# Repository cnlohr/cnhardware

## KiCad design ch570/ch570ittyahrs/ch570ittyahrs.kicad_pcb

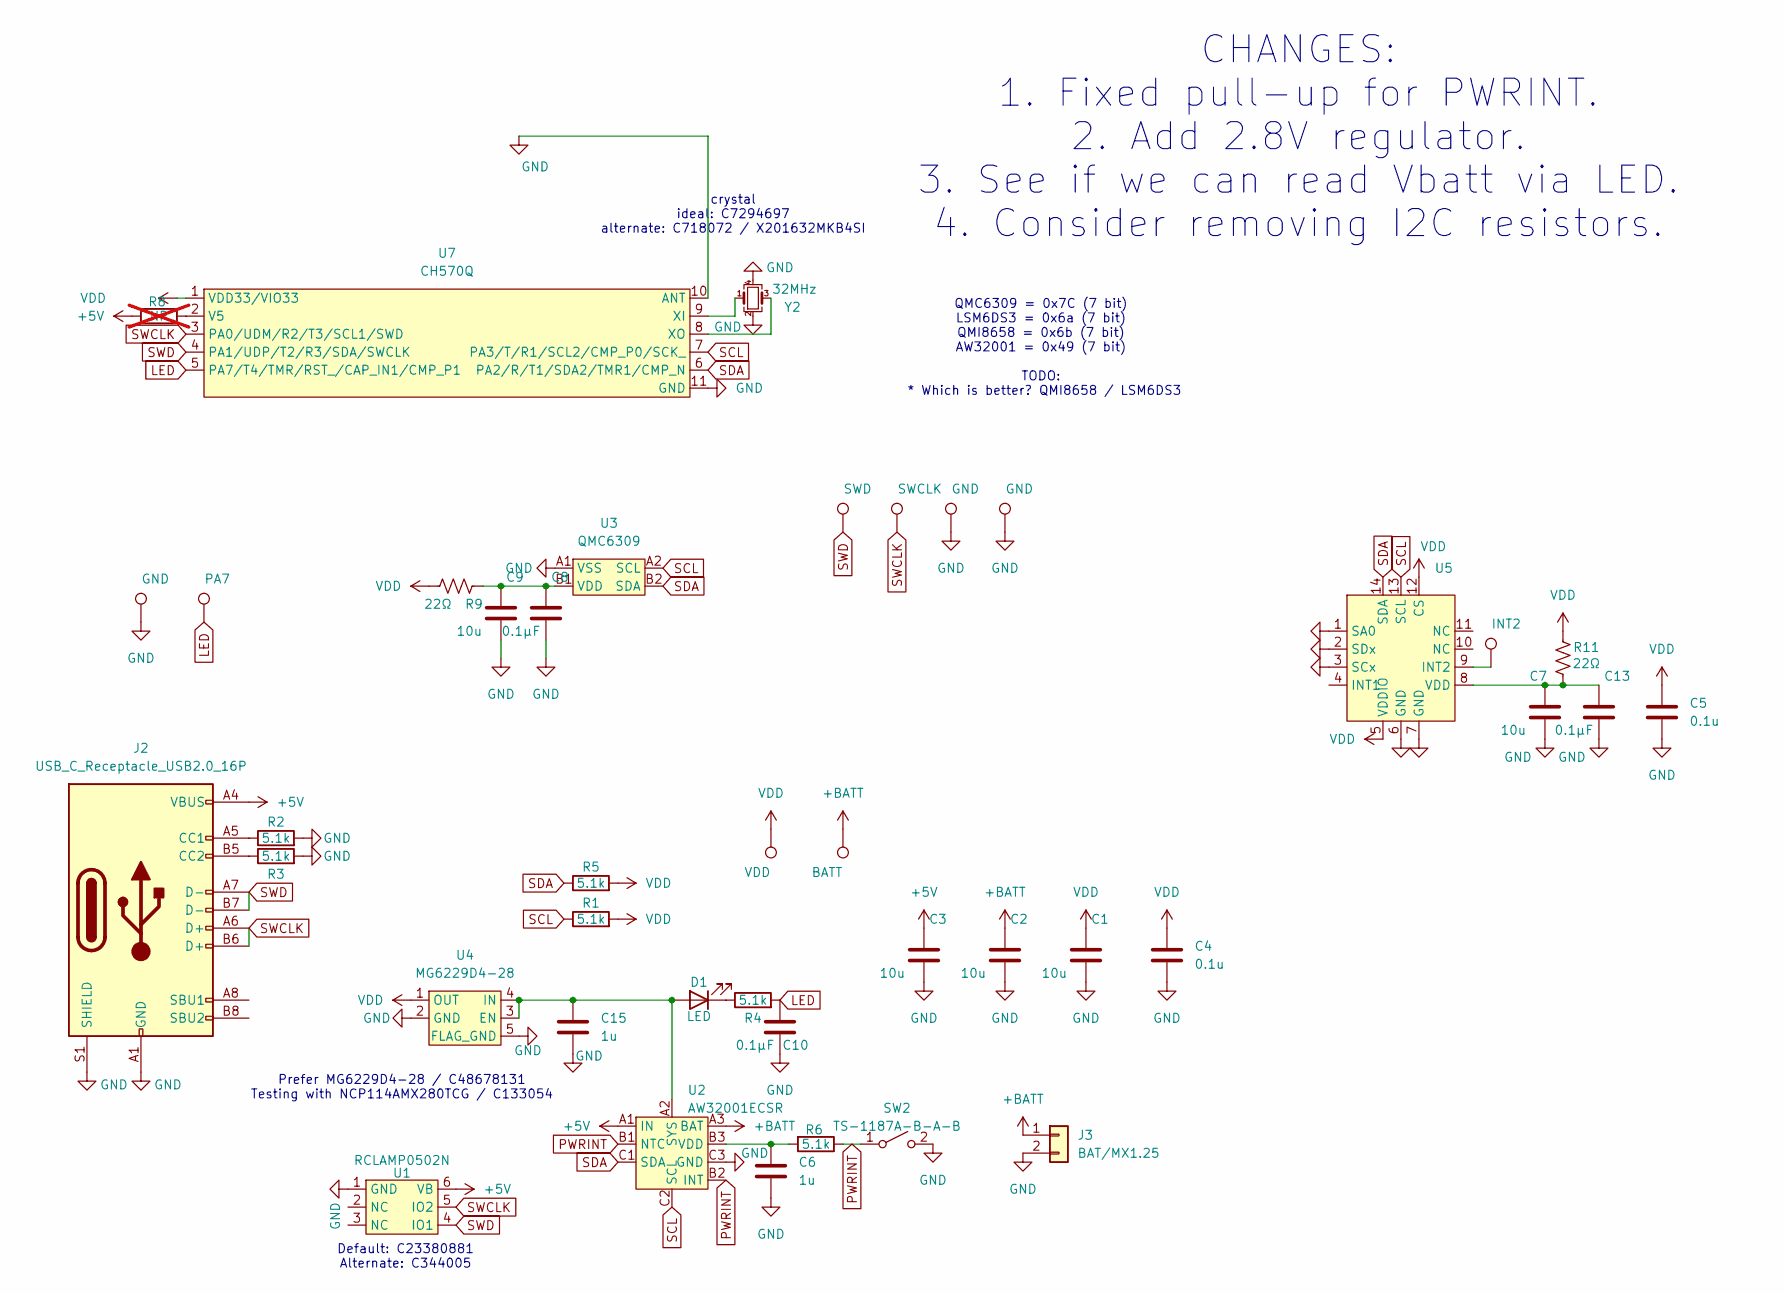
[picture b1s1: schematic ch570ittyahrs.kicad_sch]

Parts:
C1, C2, C3, C7, C9: 10u; C_0402_1005Metric; LCSC C15525
C4, C5: 0.1u; C_0402_1005Metric; LCSC C1525
C6, C15: 1u; C_0402_1005Metric; LCSC C52923
C8, C10, C13: 0.1μF; C_0402_1005Metric; LCSC C1525
D1: LED; LED_0603_1608Metric; LCSC C2290
J2: USB_C_Receptacle_USB2.0_16P; USB_C_MOD_Receptacle_HRO_TYPE-C-31-M-12; LCSC C2765186
J3: BAT/MX1.25; Hirose_DF13C_CL535-0402-2-51_1x02-1MP_P1.25mm_Vertical; LCSC C3029359
R1, R2, R3, R4, R5, R6: 5.1k; R_0402_1005Metric; LCSC C25905
R8: NP; R_0402_1005Metric; not fitted
R9, R11: 22Ω; R_0402_1005Metric_COMPACT; LCSC C25092
SW2: TS-1187A-B-A-B; SW_SPST_TL3342; LCSC C318884
TP1: INT2; TestPoint_Pad_D1.0mm
TP2: SWD; TestPoint_Pad_D1.0mm
TP3: SWCLK; TestPoint_Pad_D1.0mm
TP4, TP5, TP7: GND; TestPoint_Pad_D1.0mm
TP6: PA7; TestPoint_Pad_D1.0mm
TP8: VDD; TestPoint_Pad_D1.0mm
TP9: BATT; TestPoint_Pad_D1.0mm
U1: RCLAMP0502N; DFN-6_1.2x1.0mm_P0.4mm; LCSC C23380881
U2: AW32001ECSR; WLCSP-9-P0.5mm; LCSC C5125890
U3: QMC6309; WLP-4_0.83x0.83mm_P0.4mm; LCSC C5439871
U4: MG6229D4-28; xdfn-reg; LCSC C48678131
U5: LGA-14_3x2.5mm_P0.5mm_LayoutBorder3x4y_EVEN_PADS; LCSC C967633
U7: CH570Q; DFN-10-1EP_3x3mm_P0.5mm_EP1.7x2.5mm; LCSC C49260680
Y2: 32MHz; Crystal_SMD_2016-4Pin_2.0x1.6mm; LCSC C7294697

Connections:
+5V: C3.1, J2.A4 (VBUS), J2.A9 (VBUS), J2.B4 (VBUS), J2.B9 (VBUS), R8.2, U1.6 (VB), U2.A1 (IN)
+BATT: C2.1, J3.1, TP9.1, U2.A3 (BAT)
GND: C1.2, C2.2, C3.2, C4.2, C5.2, C6.2, C7.2, C8.2, C9.2, C10.2, C13.2, C15.2, J2.A1 (GND), J2.A12 (GND), J2.B1 (GND), J2.B12 (GND), J2.S1 (SHIELD), J3.2, R2.2, R3.2, SW2.2 (B), TP4.1, TP5.1, TP7.1, U1.1 (GND), U2.C3 (GND), U3.A1 (VSS), U4.2 (GND), U4.5 (FLAG_GND), U5.1 (SA0), U5.2 (SDx), U5.3 (SCx), U5.6 (GND), U5.7 (GND), U7.10 (ANT), U7.11 (GND), Y2.2, Y2.4
LED: C10.1, R4.2, TP6.1, U7.5 (PA7/T4/TMR/RST_/CAP_IN1/CMP_P1)
unnamed: C15.1, D1.2 (A), U2.A2 (SYS), U4.3 (EN), U4.4 (IN)
unnamed: D1.1 (K), R4.1
unnamed: J2.A5 (CC1), R2.1
unnamed: J2.B5 (CC2), R3.1
unnamed: C6.1, R6.2, U2.B3 (VDD)
unnamed: C8.1, C9.1, R9.1, U3.B1 (VDD)
unnamed: TP1.1, U5.9 (INT2)
unnamed: C7.1, C13.1, R11.2, U5.8 (VDD)
unnamed: R8.1, U7.2 (V5)
unnamed: U7.9 (XI), Y2.1
unnamed: U7.8 (XO), Y2.3
PWRINT: R6.1, SW2.1 (A), U2.B1 (NTC), U2.B2 (INT)
SCL: R1.1, U2.C2 (SCL), U3.A2 (SCL), U5.13 (SCL), U7.7 (PA3/T/R1/SCL2/CMP_P0/SCK_)
SDA: R5.1, U2.C1 (SDA), U3.B2 (SDA), U5.14 (SDA), U7.6 (PA2/R/T1/SDA2/TMR1/CMP_N)
SWCLK: J2.A6 (D+), J2.B6 (D+), TP3.1, U1.5 (IO2), U7.3 (PA0/UDM/R2/T3/SCL1/SWD)
SWD: J2.A7 (D-), J2.B7 (D-), TP2.1, U1.4 (IO1), U7.4 (PA1/UDP/T2/R3/SDA/SWCLK)
VDD: C1.1, C4.1, C5.1, R1.2, R5.2, R9.2, R11.1, TP8.1, U4.1 (OUT), U5.5 (VDDIO), U5.12 (CS), U7.1 (VDD33/VIO33)

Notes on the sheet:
Prefer MG6229D4-28 / C48678131 Testing with NCP114AMX280TCG / C133054
QMC6309 = 0x7C (7 bit) LSM6DS3 = 0x6a (7 bit) QMI8658 = 0x6b (7 bit) AW32001 = 0x49 (7 bit) TODO: * Which is better? QMI8658 / LSM6DS3
crystal ideal: C7294697 alternate: C718072 / X201632MKB4SI
Default: C23380881 Alternate: C344005
CHANGES: 1. Fixed pull-up for PWRINT. 2. Add 2.8V regulator. 3. See if we can read Vbatt via LED. 4. Consider removing I2C resistors.

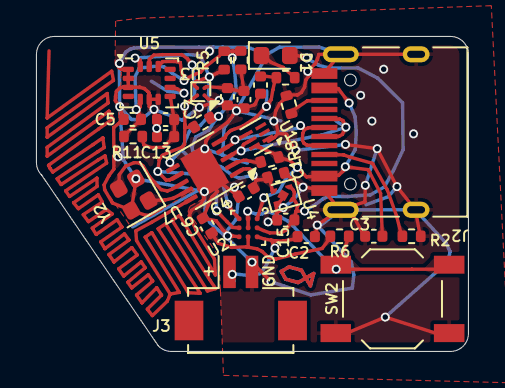
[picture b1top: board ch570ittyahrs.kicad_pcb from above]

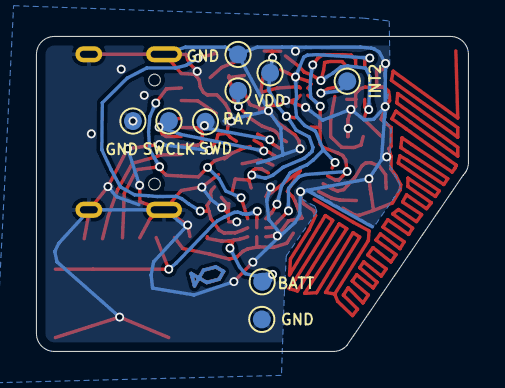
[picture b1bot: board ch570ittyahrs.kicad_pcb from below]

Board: 2 copper layers, 24.0 x 17.5 mm, 41 parts (9 on the bottom side), 21 nets.

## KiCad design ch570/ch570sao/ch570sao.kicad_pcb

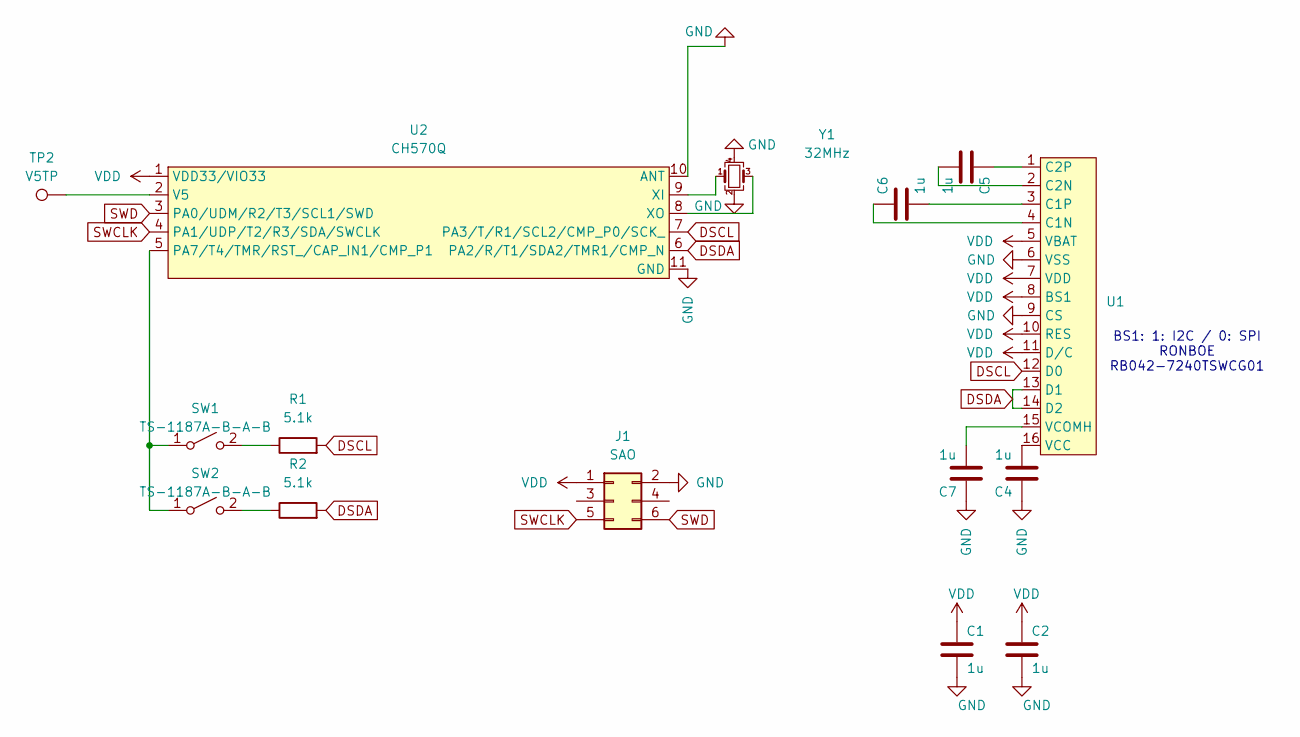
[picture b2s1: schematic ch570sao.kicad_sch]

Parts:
C1, C2, C4, C5, C6, C7: 1u; R_0402_1005Metric; LCSC C52923
J1: SAO; PinHeader_2x03_P2.54mm_Vertical_SMD
R1, R2: 5.1k; R_0402_1005Metric; LCSC C25905
SW1, SW2: TS-1187A-B-A-B; SW_SPST_TL3342; LCSC C318884
TP2: V5TP; TestPoint_Pad_D1.0mm
U1: P0.65mm_16_pin_OLED_FLEX_CONTACT
U2: CH570Q; DFN-10-1EP_3x3mm_P0.5mm_EP1.7x2.5mm; LCSC C49260680
Y1: 32MHz; Crystal_SMD_2016-4Pin_2.0x1.6mm; LCSC C7294697

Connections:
DSCL: R1.2, U1.12 (D0), U2.7 (PA3/T/R1/SCL2/CMP_P0/SCK_)
DSDA: R2.2, U1.13 (D1), U1.14 (D2), U2.6 (PA2/R/T1/SDA2/TMR1/CMP_N)
GND: C1.1, C2.1, C4.2, C7.2, J1.2, U1.6 (VSS), U1.9 (CS), U2.10 (ANT), U2.11 (GND), Y1.2, Y1.4
unnamed: SW1.1 (A), SW2.1 (A), U2.5 (PA7/T4/TMR/RST_/CAP_IN1/CMP_P1)
unnamed: R1.1, SW1.2 (B)
unnamed: R2.1, SW2.2 (B)
unnamed: C6.2, U1.4 (C1N)
unnamed: C6.1, U1.3 (C1P)
unnamed: C5.1, U1.2 (C2N)
unnamed: C5.2, U1.1 (C2P)
unnamed: C4.1, U1.16 (VCC)
unnamed: C7.1, U1.15 (VCOMH)
unnamed: TP2.1, U2.2 (V5)
unnamed: U2.9 (XI), Y1.1
unnamed: U2.8 (XO), Y1.3
SWCLK: J1.5, U2.4 (PA1/UDP/T2/R3/SDA/SWCLK)
SWD: J1.6, U2.3 (PA0/UDM/R2/T3/SCL1/SWD)
VDD: C1.2, C2.2, J1.1, U1.5 (VBAT), U1.7 (VDD), U1.8 (BS1), U1.10 (RES), U1.11 (D/C), U2.1 (VDD33/VIO33)

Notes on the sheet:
BS1: 1: I2C / 0: SPI RONBOE RB042-7240TSWCG01

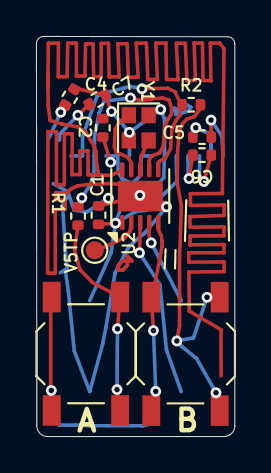
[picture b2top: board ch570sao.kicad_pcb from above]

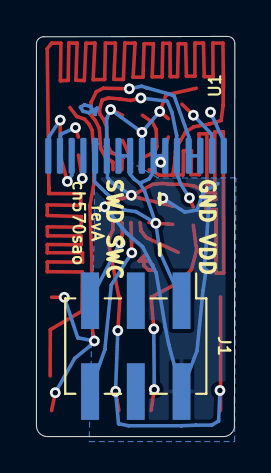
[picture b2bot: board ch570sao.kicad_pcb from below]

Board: 2 copper layers, 11.0 x 22.2 mm, 15 parts (2 on the bottom side), 18 nets.

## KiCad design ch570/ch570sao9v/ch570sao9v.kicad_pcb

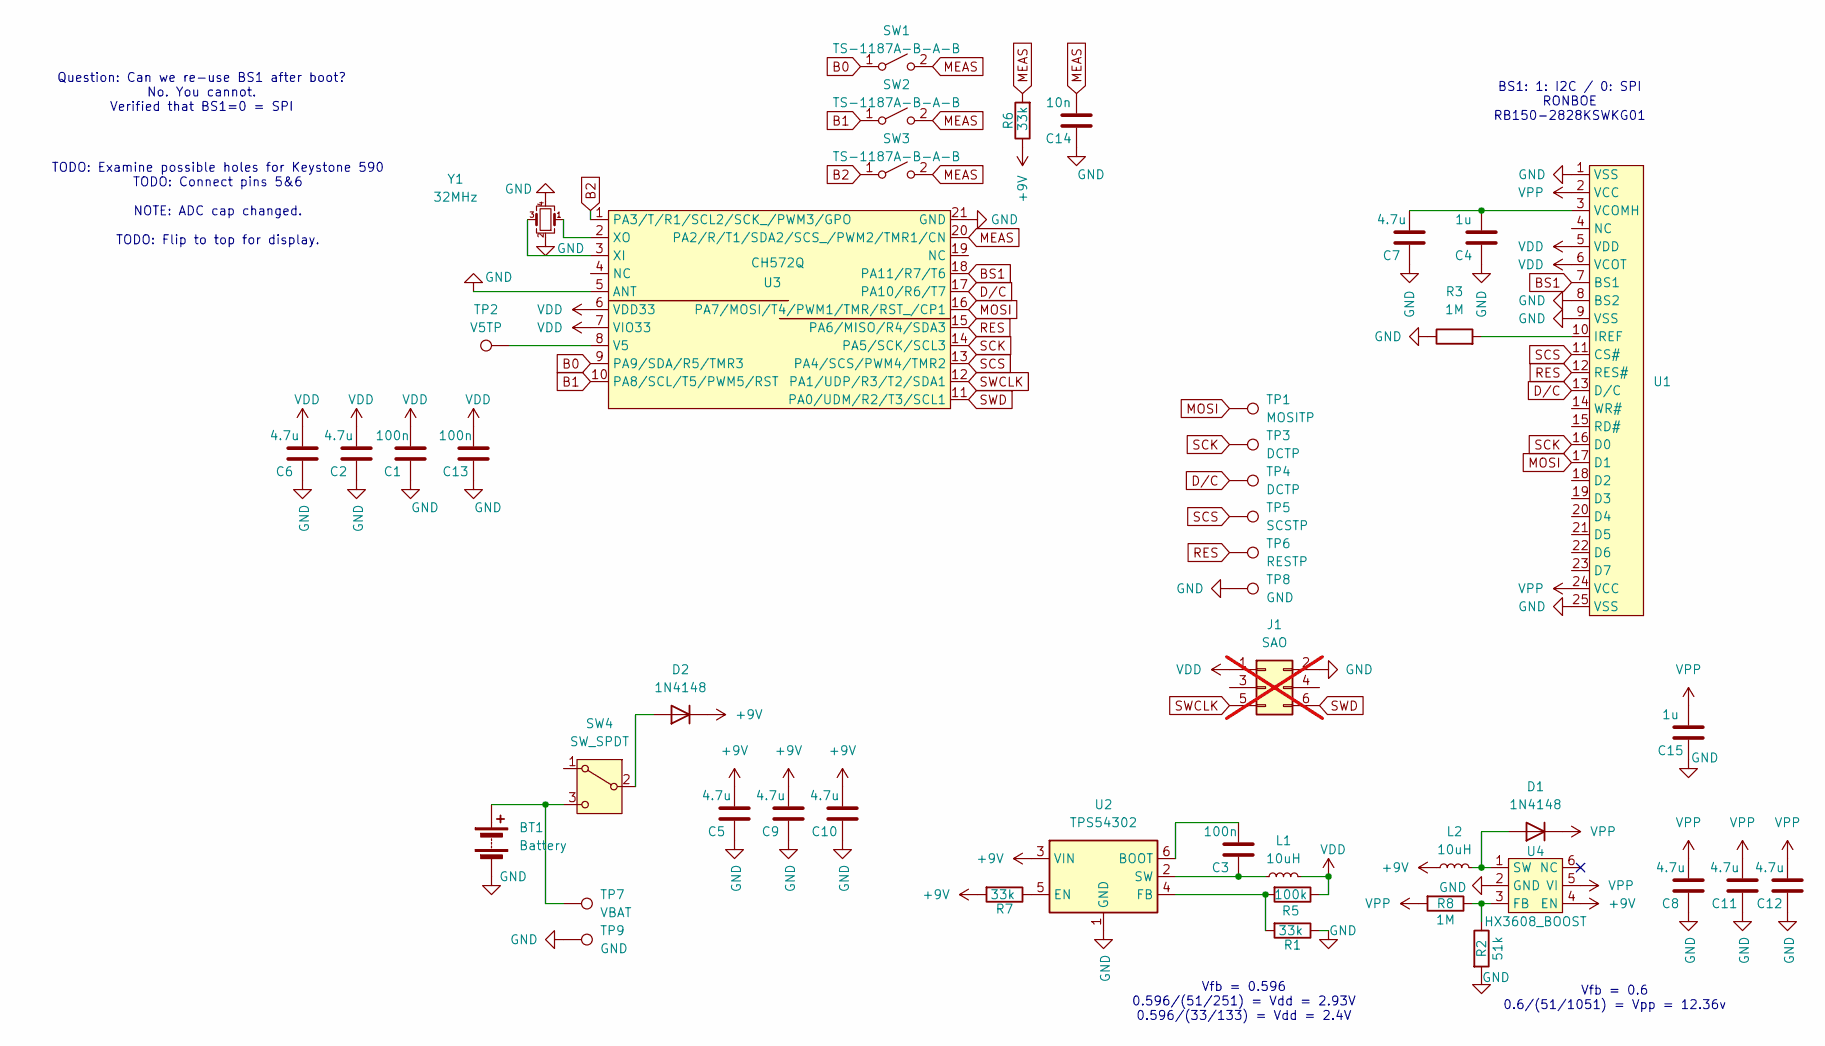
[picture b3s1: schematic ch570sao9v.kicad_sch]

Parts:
BT1: Battery
C1, C3, C13: 100n; R_0402_1005Metric; LCSC C307331
C2, C5, C6, C7, C8, C9, C10, C11, C12: 4.7u; C_1206_3216Metric; LCSC C29823
C4, C15: 1u; R_0402_1005Metric; LCSC C52923
C14: 10n; R_0402_1005Metric; LCSC C15195
D1, D2: 1N4148; D_SOD-323; LCSC C2128
J1: SAO; PinHeader_2x03_P2.54mm_Vertical_SMD; not fitted
L1, L2: 10uH; L_1008_2520Metric; LCSC C37428
R1, R6, R7: 33k; R_0402_1005Metric_COMPACT; LCSC C25779
R2: 51k; R_0402_1005Metric_COMPACT; LCSC C25794
R3, R8: 1M; R_0402_1005Metric_COMPACT; LCSC C26083
R5: 100k; R_0402_1005Metric_COMPACT; LCSC C25741
SW1, SW2, SW3: TS-1187A-B-A-B; BTC007_Button_Silicone
SW4: SW_SPDT; SW_SPDT_PCM12; LCSC C963206
TP1: MOSITP; TestPoint_Pad_D1.0mm
TP2: V5TP; TestPoint_Pad_D1.0mm
TP3, TP4: DCTP; TestPoint_Pad_D1.0mm
TP5: SCSTP; TestPoint_Pad_D1.0mm
TP6: RESTP; TestPoint_Pad_D1.0mm
TP7: VBAT; TestPoint_Pad_D1.0mm
TP8, TP9: GND; TestPoint_Pad_D1.0mm
U1: RB150-2828KSWKG01
U2: TPS54302; SOT-23-6; LCSC C311983
U3: CH572Q; QFN-20-1EP_3x3mm_P0.4mm_EP1.65x1.65mm; LCSC C46597863
U4: HX3608_BOOST; SOT-23-6; LCSC C296278
Y1: 32MHz; Crystal_SMD_2016-4Pin_2.0x1.6mm; LCSC C7294697

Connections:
+9V: C5.1, C9.1, C10.1, D2.1 (K), D2.2 (A), L2.1, R6.1, R7.2, SW4.2 (B), U2.3 (VIN), U4.4 (EN)
B0: SW1.1 (A), U3.9 (PA9/SDA/R5/TMR3)
B1: SW2.1 (A), U3.10 (PA8/SCL/T5/PWM5/RST)
B2: SW3.1 (A), U3.1 (PA3/T/R1/SCL2/SCK_/PWM3/GPO)
BS1: U1.7 (BS1), U3.18 (PA11/R7/T6)
D/C: TP4.1, U1.13 (D/C), U3.17 (PA10/R6/T7)
GND: BT1.2 (-), C1.2, C2.2, C4.2, C5.2, C6.2, C7.2, C8.2, C9.2, C10.2, C11.2, C12.2, C13.2, C14.2, C15.2, J1.2, R1.1, R2.2, R3.1, TP8.1, TP9.1, U1.1 (VSS), U1.8 (BS2), U1.9 (VSS), U1.25 (VSS), U2.1 (GND), U3.5 (ANT), U3.21 (GND), U4.2 (GND), Y1.2, Y1.4
MEAS: C14.1, R6.2, SW1.2 (B), SW2.2 (B), SW3.2 (B), U3.20 (PA2/R/T1/SDA2/SCS_/PWM2/TMR1/CN)
MOSI: TP1.1, U1.17 (D1), U3.16 (PA7/MOSI/T4/PWM1/TMR/RST_/CP1)
unnamed: BT1.1 (+), SW4.3 (C), TP7.1
unnamed: D1.2 (A), L2.2, U4.1 (SW)
unnamed: R3.2, U1.10 (IREF)
unnamed: C4.1, C7.1, U1.3 (VCOMH)
unnamed: C3.1, U2.6 (BOOT)
unnamed: R7.1, U2.5 (EN)
unnamed: R1.2, R5.2, U2.4 (FB)
unnamed: C3.2, L1.1, U2.2 (SW)
unnamed: TP2.1, U3.8 (V5)
unnamed: U3.3 (XI), Y1.3
unnamed: U3.2 (XO), Y1.1
unnamed: R2.1, R8.1, U4.3 (FB)
RES: TP6.1, U1.12 (RES#), U3.15 (PA6/MISO/R4/SDA3)
SCK: TP3.1, U1.16 (D0), U3.14 (PA5/SCK/SCL3)
SCS: TP5.1, U1.11 (CS#), U3.13 (PA4/SCS/PWM4/TMR2)
SWCLK: J1.5, U3.12 (PA1/UDP/R3/T2/SDA1)
SWD: J1.6, U3.11 (PA0/UDM/R2/T3/SCL1)
VDD: C1.1, C2.1, C6.1, C13.1, J1.1, L1.2, R5.1, U1.5 (VDD), U1.6 (VCOT), U3.6 (VDD33), U3.7 (VIO33)
VPP: C8.1, C11.1, C12.1, C15.1, D1.1 (K), R8.2, U1.2 (VCC), U1.24 (VCC), U4.5 (VI)

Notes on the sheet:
TODO: Examine possible holes for Keystone 590 TODO: Connect pins 5&6 NOTE: ADC cap changed. TODO: Flip to top for display.
Question: Can we re-use BS1 after boot? No. You cannot. Verified that BS1=0 = SPI
Vfb = 0.596 0.596/(51/251) = Vdd = 2.93V 0.596/(33/133) = Vdd = 2.4V
Vfb = 0.6 0.6/(51/1051) = Vpp = 12.36v
BS1: 1: I2C / 0: SPI RONBOE RB150-2828KSWKG01

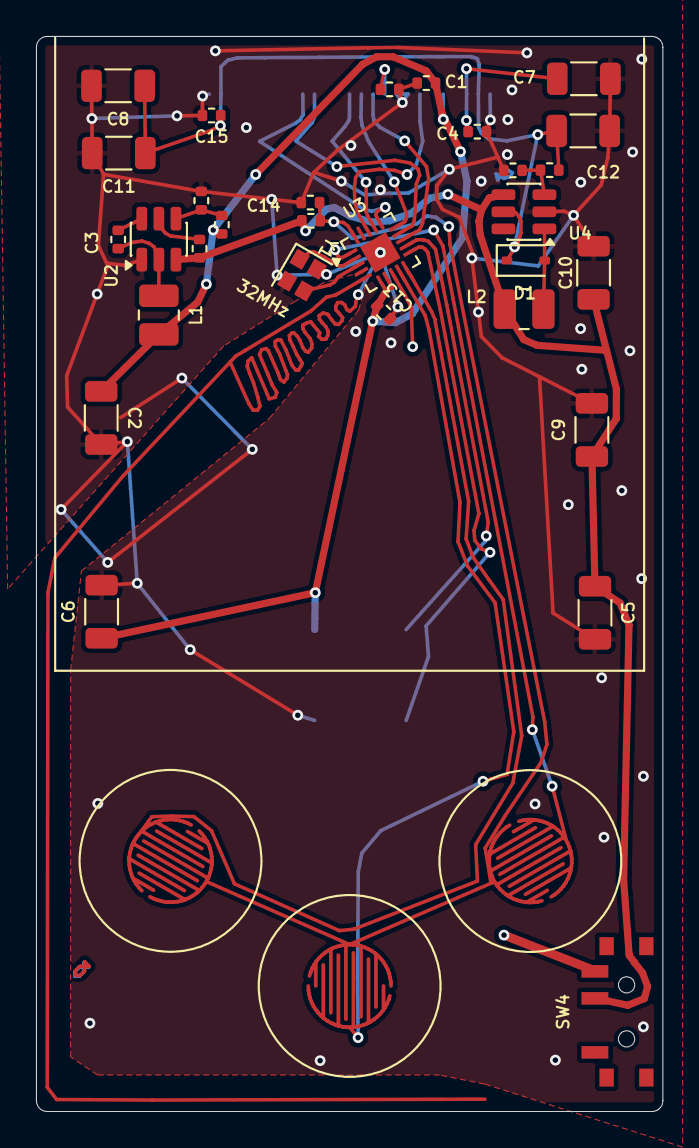
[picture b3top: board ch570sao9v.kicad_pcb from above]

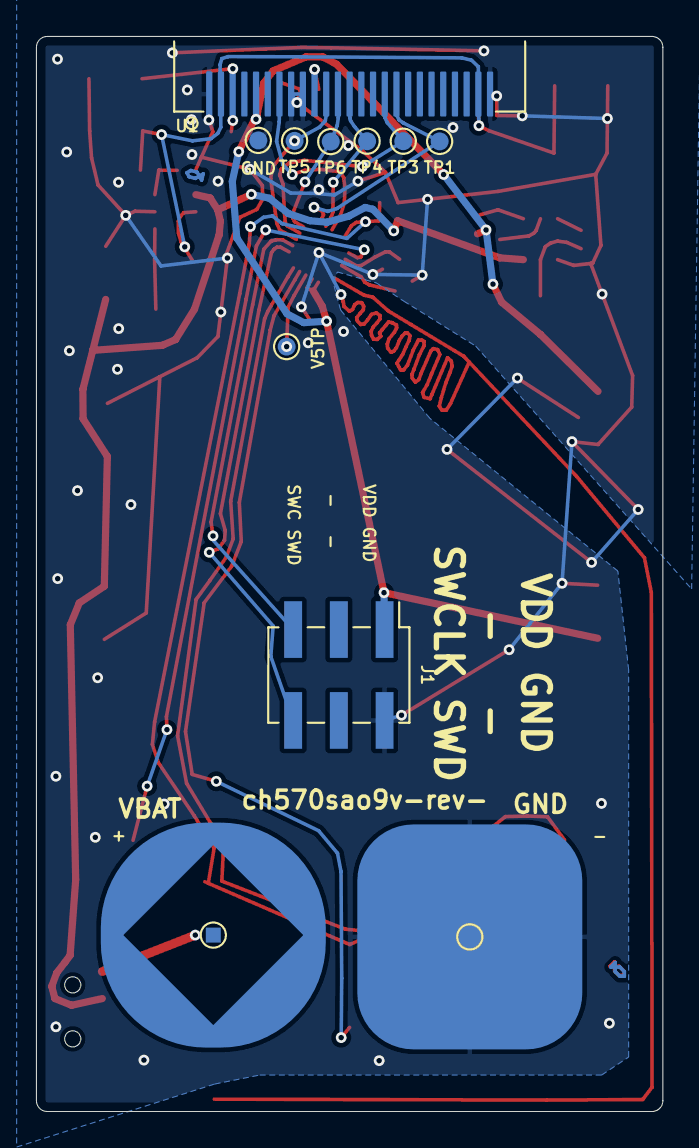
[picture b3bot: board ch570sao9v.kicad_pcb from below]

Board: 2 copper layers, 34.8 x 59.7 mm, 44 parts (11 on the bottom side), 28 nets.

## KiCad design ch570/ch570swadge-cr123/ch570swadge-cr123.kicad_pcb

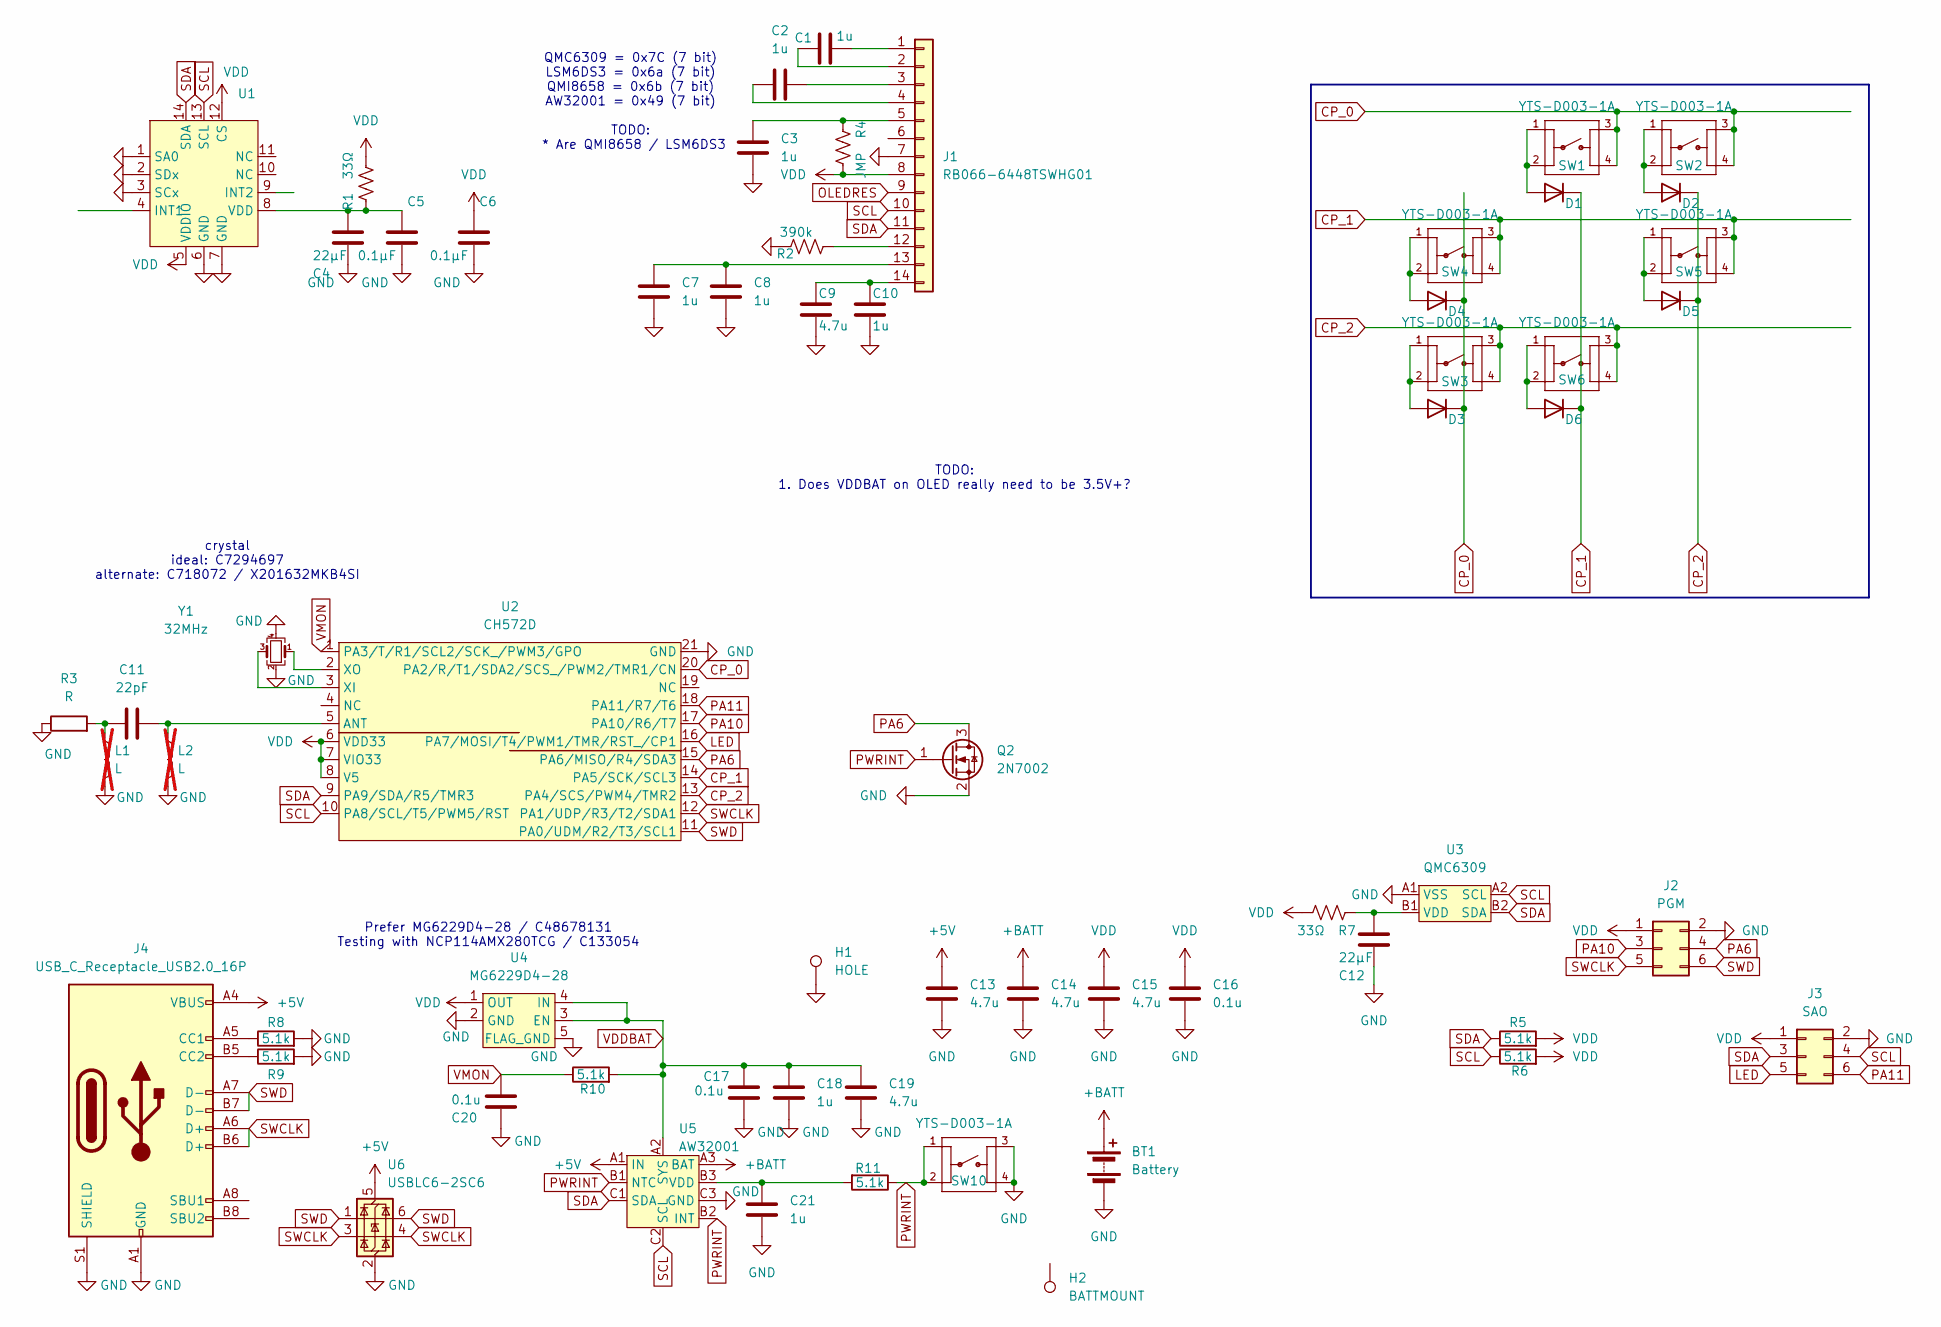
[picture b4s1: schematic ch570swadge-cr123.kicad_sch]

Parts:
BT1: Battery; BatteryHolder_Bulgin_BX0123_1xCR123; LCSC C5290177
C1, C2, C3, C7, C8, C10, C18, C21: 1u; C_0402_1005Metric; LCSC C52923
C4, C12: 22μF; C_0603_1608Metric; LCSC C59461
C5, C6: 0.1μF; C_0402_1005Metric; LCSC C307331
C9, C13, C14, C15, C19: 4.7u; C_0402_1005Metric; LCSC C368809
C11: 22pF; C_0402_1005Metric; LCSC C1555
C16, C17, C20: 0.1u; C_0402_1005Metric; LCSC C307331
D1, D2, D3, D4, D5, D6: 1N4148WS; D_SOD-323_HandSoldering; LCSC C2128
H1: HOLE; MountingHole_5.3mm_M5_DIN965_Pad
H2: BATTMOUNT; MountingHole_2.1mm
J1: RB066-6448TSWHG01
J2: PGM; PinHeader_2x03_P2.54mm_Vertical_SMD; LCSC C192301
J3: SAO; PinHeader_2x03_P2.54mm_Vertical_SMD; LCSC C192301
J4: USB_C_Receptacle_USB2.0_16P; USB_C_MOD_Receptacle_HRO_TYPE-C-31-M-12; LCSC C2765186
L1, L2: L; L_0402_1005Metric; not fitted
Q2: 2N7002; SOT-23; LCSC C8545
R1, R7: 33Ω; R_0603_1608Metric; LCSC C23140
R2: 390k; R_0402_1005Metric_COMPACT; LCSC C25782
R3: R; Texas_SWRA117D_2.4GHz_Right
R4: JMP; R_0603_1608Metric; LCSC C21189
R5, R6, R8, R9, R10, R11: 5.1k; R_0402_1005Metric; LCSC C25905
SW1, SW2, SW3, SW4, SW5, SW6, SW10: YTS-D003-1A; Digikey 2223-TS04-66-65-BK-100-SMT-ND
U1: LGA-14_3x2.5mm_P0.5mm_LayoutBorder3x4y_EVEN_PADS; LCSC C967633
U2: CH572D; QFN-20-1EP_3x3mm_P0.4mm_EP1.65x1.65mm; LCSC C46597863
U3: QMC6309; WLP-4_0.83x0.83mm_P0.4mm; LCSC C5439871
U4: MG6229D4-28; xdfn-reg; LCSC C48678131
U5: AW32001; WLCSP-9-P0.5mm; LCSC C5125890
U6: USBLC6-2SC6; SOT-363_SC-70-6; LCSC C1973965
Y1: 32MHz; Crystal_SMD_2016-4Pin_2.0x1.6mm; LCSC C7294697

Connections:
+5V: C13.1, J4.A4 (VBUS), J4.A9 (VBUS), J4.B4 (VBUS), J4.B9 (VBUS), U5.A1 (IN), U6.5 (VBUS)
+BATT: BT1.1 (+), C14.1, U5.A3 (BAT)
CP_0: D3.1 (K), D4.1 (K), SW1.3, SW1.4, SW2.3, SW2.4, U2.20 (PA2/R/T1/SDA2/SCS_/PWM2/TMR1/CN)
CP_1: D1.1 (K), D6.1 (K), SW4.3, SW4.4, SW5.3, SW5.4, U2.14 (PA5/SCK/SCL3)
CP_2: D2.1 (K), D5.1 (K), SW3.3, SW3.4, SW6.3, SW6.4, U2.13 (PA4/SCS/PWM4/TMR2)
GND: BT1.2 (-), C3.2, C4.2, C5.2, C6.2, C7.2, C8.2, C9.2, C10.2, C12.2, C13.2, C14.2, C15.2, C16.2, C17.2, C18.2, C19.2, C20.2, C21.2, H1.1, J1.7, J2.2, J3.2, J4.A1 (GND), J4.A12 (GND), J4.B1 (GND), J4.B12 (GND), J4.S1 (SHIELD), L1.2, L2.2, Q2.2 (S), R2.2, R3.1, R8.2, R9.2, SW10.3, SW10.4, U1.1 (SA0), U1.2 (SDx), U1.3 (SCx), U1.6 (GND), U1.7 (GND), U2.21 (GND), U3.A1 (VSS), U4.2 (GND), U4.5 (FLAG_GND), U5.C3 (GND), U6.2 (GND), Y1.2, Y1.4
LED: J3.5, U2.16 (PA7/MOSI/T4/PWM1/TMR/RST_/CP1)
unnamed: C11.1, L1.1, R3.2
unnamed: D1.2 (A), SW1.1, SW1.2
unnamed: D2.2 (A), SW2.1, SW2.2
unnamed: D3.2 (A), SW3.1, SW3.2
unnamed: D4.2 (A), SW4.1, SW4.2
unnamed: D5.2 (A), SW5.1, SW5.2
unnamed: D6.2 (A), SW6.1, SW6.2
unnamed: C1.2, J1.1
unnamed: C1.1, J1.2
unnamed: C2.2, J1.3
unnamed: C2.1, J1.4
unnamed: C3.1, J1.5, R4.1
unnamed: J1.12, R2.1
unnamed: C7.1, C8.1, J1.13
unnamed: C9.1, C10.1, J1.14
unnamed: J4.A5 (CC1), R8.1
unnamed: J4.B5 (CC2), R9.1
unnamed: C4.1, C5.1, R1.1, U1.8 (VDD)
unnamed: C11.2, L2.1, U2.5 (ANT)
unnamed: U2.3 (XI), Y1.3
unnamed: U2.2 (XO), Y1.1
unnamed: C12.1, R7.1, U3.B1 (VDD)
unnamed: C21.1, R11.2, U5.B3 (VDD)
OLEDRES: J1.9
PA6: J2.4, Q2.3 (D), U2.15 (PA6/MISO/R4/SDA3)
PA10: J2.3, U2.17 (PA10/R6/T7)
PA11: J3.6, U2.18 (PA11/R7/T6)
PWRINT: Q2.1 (G), R11.1, SW10.1, SW10.2, U5.B1 (NTC), U5.B2 (INT)
SCL: J1.10, J3.4, R6.1, U1.13 (SCL), U2.10 (PA8/SCL/T5/PWM5/RST), U3.A2 (SCL), U5.C2 (SCL)
SDA: J1.11, J3.3, R5.1, U1.14 (SDA), U2.9 (PA9/SDA/R5/TMR3), U3.B2 (SDA), U5.C1 (SDA)
SWCLK: J2.5, J4.A6 (D+), J4.B6 (D+), U2.12 (PA1/UDP/R3/T2/SDA1), U6.3 (I/O2), U6.4 (I/O2)
SWD: J2.6, J4.A7 (D-), J4.B7 (D-), U2.11 (PA0/UDM/R2/T3/SCL1), U6.1 (I/O1), U6.6 (I/O1)
VDD: C6.1, C15.1, C16.1, J1.8, J2.1, J3.1, R1.2, R4.2, R5.2, R6.2, R7.2, U1.5 (VDDIO), U1.12 (CS), U2.6 (VDD33), U2.7 (VIO33), U2.8 (V5), U4.1 (OUT)
VDDBAT: C17.1, C18.1, C19.1, R10.2, U4.3 (EN), U4.4 (IN), U5.A2 (SYS)
VMON: C20.1, R10.1, U2.1 (PA3/T/R1/SCL2/SCK_/PWM3/GPO)

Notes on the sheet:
TODO: 1. Does VDDBAT on OLED really need to be 3.5V+?
Prefer MG6229D4-28 / C48678131 Testing with NCP114AMX280TCG / C133054
QMC6309 = 0x7C (7 bit) LSM6DS3 = 0x6a (7 bit) QMI8658 = 0x6b (7 bit) AW32001 = 0x49 (7 bit) TODO: * Are QMI8658 / LSM6DS3
crystal ideal: C7294697 alternate: C718072 / X201632MKB4SI

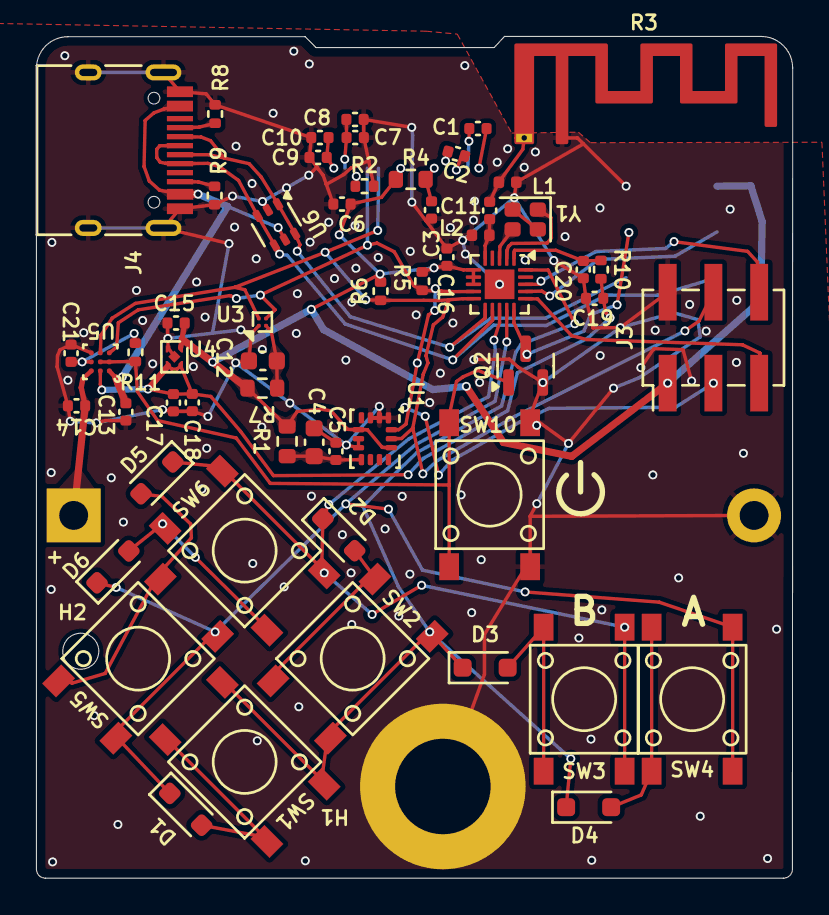
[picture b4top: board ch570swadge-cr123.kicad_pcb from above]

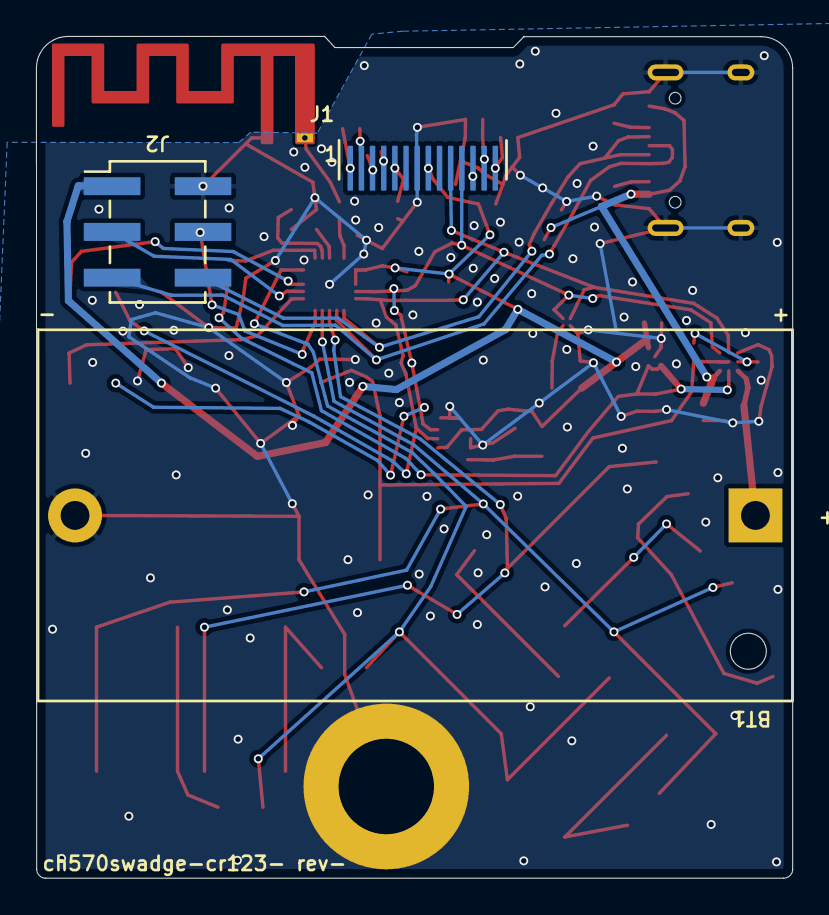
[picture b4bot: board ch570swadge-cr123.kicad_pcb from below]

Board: 2 copper layers, 42.0 x 46.8 mm, 62 parts (3 on the bottom side), 41 nets.
